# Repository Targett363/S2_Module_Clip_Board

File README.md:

# S2_Module_Clip_Board
Clip in programmer/prototyping board for ESP32-S2 modules

What is it?

This board will allow you to clip in an ESP32-S2 WROOM or WROVER module for programming and testing. Slot the module into the pins where it will be held securely while you upload your code.

The Board has two USB micro sockets: The first is connected to a CP2104 USB to UART to upload of your firmware and receive serial messages. The second is directly connected to GPIO19 & 20 that are the onboard USB - & + pins.

The board can be powered from either of the USB sockets, the UART USB has a power switch and the S2 USB will directly power the board. These sockets are separated by diodes so neither can reverse power the other. The S2 USB has bridgeable solder pads so that it can be used to supply USB power if acting as OTG Host.

The CP2104 handles the USB to UART conversion as well as putting the module into "programming mode".

Where Espressif have enabled programming via the S2 USB and the module can be put in "programming mode" using the IO_0 and Reset buttons.

All GPIO pins are broken out to 2.54mm header pins. Caution should be taken as some pins are used by the WROVER module for PSRAM.

Why did you make it?

I made the V0.1 board as a personal challenge, just to see if I could. Then as I chatted with other makers I became a little more serious about designing this for more general use. V0.2 provided a reasonable working prototype and with V0.3 I think it's ready for public consumption.

What makes it special?

As far as I know, this is the only available board of it's type at the moment.

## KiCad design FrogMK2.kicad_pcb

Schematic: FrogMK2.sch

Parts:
C1, C2, C3, C8: 10uF; C_0603_1608Metric
C4, C7, C9: 0.1uF; C_0603_1608Metric
C5, C6: 12pF; C_0603_1608Metric
D1, D2, D3: LED; LED_0603_1608Metric
D4, D5: D; D_SMB
IO_0: SW_Push; SW_Push_1P1T_NO_CK_KMR2
J1, J5: Conn_01x16; PinSocket_1x16_P2.54mm_Vertical
J2: Conn_01x10; PinSocket_1x10_P2.54mm_Vertical
J3: USB_OTG; USB-MicroB_U253-051T-4BH85-SB
J8: USB_PROG; USB-MicroB_U253-051T-4BH85-SB
JP1: SolderJumper_2_Open; SolderJumper-2_P1.3mm_Open_TrianglePad1.0x1.5mm
Q1: MUN5211DW1; SOT-363_SC-70-6
Q2: Q_PMOS_GSD; SOT-23
R1, R2: 10K; R_0603_1608Metric
R4, R5, R6: 180; R_0603_1608Metric
Reset1: SW_Push; SW_Push_1P1T_NO_CK_KMR2
SW3: SW_SPDT; SW_SPDT_PCM12
U1: LT1963AxST-3.3; SOT-223-3_TabPin2
U2: ESP32-S2; ESP32-S2-Wrover_Frog-Pins
U3: CP2104; QFN-24-1EP_4x4mm_P0.5mm_EP2.6x2.6mm
Y1: 32.768KHz; Crystal_SMD_G8-2Pin_3.2x1.5mm

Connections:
+3V3: C2.1, C3.1, C4.1, C8.1, J1.2, R1.1, R2.1, U1.3, U2.2 (3V3), U3.5, U3.6
+5V: D5.1, Q2.2, SW3.1
DIN+: J8.3, U3.3
DIN-: J8.2, U3.4
DOTG+: J2.4, J3.3, U2.23 (IO20)
DOTG-: J2.5, J3.2, U2.22 (IO19)
DTR: Q1.1, Q1.5, U3.23
EN: C7.2, J5.2, Q1.3, R2.2, U2.41 (EN); also elsewhere on the board
GND: C1.2, C2.2, C3.2, C4.2, C5.2, C6.2, C7.1, C8.2, C9.2, D1.1, D2.1, D3.1, IO_0.2, J1.1, J2.1, J3.5, J3.6, J5.1, J8.5, J8.6, SW3.3, U1.2, U2.1 (GND), U2.26 (GND), U2.42 (GND), U2.43 (GND), U3.2, U3.25; also elsewhere on the board
IO0: IO_0.1, J1.3, Q1.6, U2.3 (IO0)
IO1: J1.4, U2.4 (IO1)
IO2: J1.5, U2.5 (IO2)
IO3: J1.6, U2.6 (IO3)
IO4: J1.7, U2.7 (IO4)
IO5: J1.8, U2.8 (IO5)
IO6: J1.9, U2.9 (IO6)
IO7: J1.10, U2.10 (IO7)
IO8: J1.11, U2.11 (IO8)
IO9: J1.12, U2.12 (IO9)
IO10: J1.13, U2.13 (IO10)
IO11: J1.14, U2.14 (IO11)
IO12: J1.15, U2.15 (IO12)
IO13: J1.16, U2.16 (IO13)
IO14: J2.10, U2.17 (IO14)
IO17: J2.7, U2.20 (IO17)
IO18: J2.6, R1.2, U2.21 (IO18)
IO21: J2.3, U2.24 (IO21)
IO26: J2.2, U2.25 (IO26)
IO33: J5.16, U2.27 (IO33)
IO34: J5.15, U2.28 (IO34)
IO35: J5.14, U2.29 (IO35)
IO36: J5.13, U2.30 (IO36)
IO37: J5.12, U2.31 (IO37)
IO38: J5.11, U2.32 (IO38)
IO45: J5.4, U2.39 (IO45)
IO46: J5.3, U2.40 (IO46)
unnamed: C5.1, U2.18 (IO15), Y1.1
unnamed: C6.1, U2.19 (IO16), Y1.2
unnamed: D1.2, R4.2
unnamed: D2.2, R5.2
unnamed: D3.2, R6.2
unnamed 41: D4.2, J3.1; also elsewhere on the board
unnamed: D5.2, J8.1
RTS: Q1.2, Q1.4, U3.19
RX: J5.5, R6.1, U2.38 (RXD0), U3.21
TDI: J5.8, U2.35 (IO41/TDI)
TDK: J5.10, U2.33 (IO39/TCK)
TDO: J5.9, U2.34 (IO40/TDO)
TMS: J5.7, U2.36 (IO42/TMS)
TX: J5.6, R5.1, U2.37 (TXD0), U3.20
VBUS: C1.1, C9.1, D4.1, Q2.3, R4.1, U1.1, U3.7, U3.8; also elsewhere on the board
Vsig: Q2.1, SW3.2

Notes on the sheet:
Need to work out 2102n schematic from bus to esp
RX/TX should be swapped to 3.3v power out into rx/tx lines

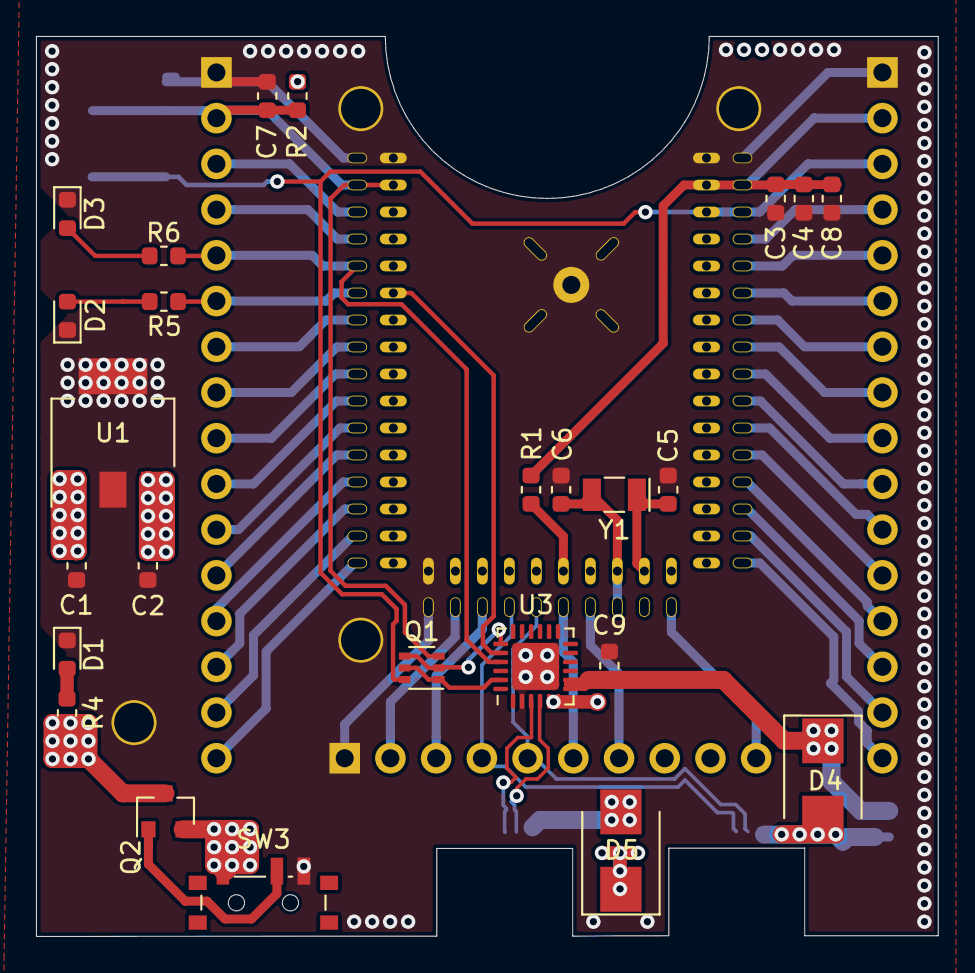
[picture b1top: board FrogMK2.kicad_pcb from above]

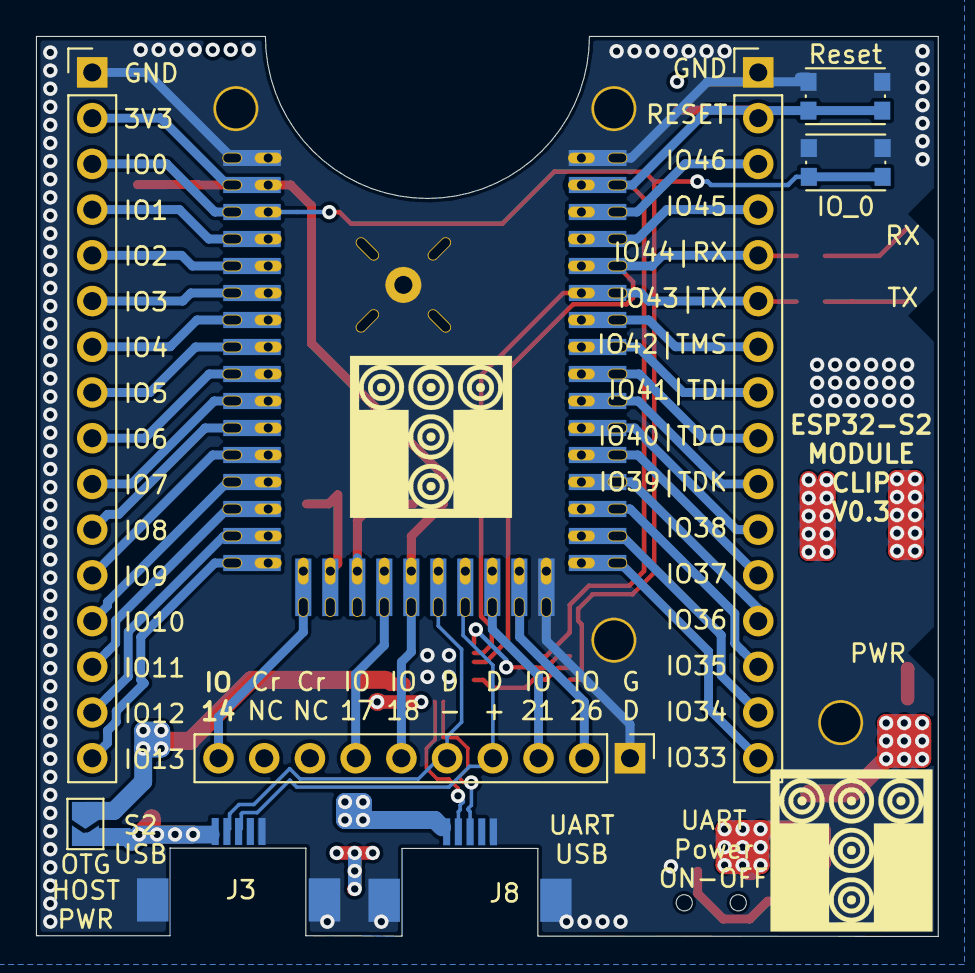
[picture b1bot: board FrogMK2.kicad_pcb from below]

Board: 4 copper layers, 50.1 x 50.0 mm, 34 parts (9 on the bottom side), 52 nets.

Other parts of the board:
OTG: SolderJumper_2_Open; SolderJumper-2_P1.3mm_Open_TrianglePad1.0x1.5mm
Reset: SW_Push; SW_Push_1P1T_NO_CK_KMR2

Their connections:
EN: Reset.1; also elsewhere on the board
GND: Reset.2; also elsewhere on the board
unnamed 41: OTG.2; also elsewhere on the board
VBUS: OTG.1; also elsewhere on the board

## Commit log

2020-10-10 Schematic in JPEG format
2020-10-10 Readme update
2020-10-14 Removing jpeg schematic
2020-10-14 Adding KiCad files
2020-10-14 Adding Licence
2020-10-20 Standardising licenese file name
2020-12-14 Adding UF2 binary files
2021-03-09 Updates
    Updates
